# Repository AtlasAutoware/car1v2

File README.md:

# Atlas car 1 v2

Car 1 v2 is the rebuild of car 1, Atlas Autoware's 1/10-scale self-driving race car: a Traxxas Slash 4x4 with a
Holmes Hobbies Puller Pro 540 motor on a carbon-fibre-printed deck, carrying car 1's RPLidar C1 and OAK-D Pro. There
is one car. This repository was named `carv2` until 11 November 2026, and its older files call the car "car v2" or
"car 2". The SICK TiM561 lidar and the LUCID Triton camera that the first design was drawn around are kept for a
later upgrade. Start at `docs/CAR1V2.md`.

Rev B (October 2026) is the electronics design car 1 v2 starts from. Its electronics are:

- **Power board (ATLAS-PWR-1).** A 4-layer board that students solder at school: the motor-bus switch with
  precharge and a hardware E-stop, the power latch, the feeds for the Jetson, lidar, camera, servo and fan, USB-C
  charging, a USB hub so one laptop cable reaches the Jetson, the ESC and the serial console, and a Raspberry Pi Pico
  that sequences it all and talks to the Jetson.
- **The Jetson Orin Nano Super on its NVIDIA dev-kit carrier,** which the team owns, on a printed tray over the power
  board.
- **The team's Flipsky Mini FSESC 6.7 Pro** as the ESC (VESC firmware, the same UART commands as car 1).
- **A JBD 4S smart BMS** with the built-in 4S3P 18650 pack.

`docs/REV_B.md` has the whole design and why it changed. Rev A (two custom boards: a 6-layer drive board with the ESC
on it and an 8-layer Jetson carrier) was finished in September, quoted by PCBWay at $1,927.81 for one assembled set,
and is kept in the repo as history.

The picture is car 1 v2 as designed on 9 November 2026 (`share/car1v2_scene.py`, `share/render_car.py`). Bought
parts are stand-ins, and the battery, the BMS, the fuse and the cables are not drawn. The rev A renders are
`share/car_*.png`.

## Status

**11 November 2026: the repository is renamed from `carv2` to `car1v2`.** GitHub redirects the old address. Whole-car
renders of car 1 v2 are in `share/car1v2_*.png`, and KiCad 3D renders of the power board are in
`boards/power/out/render/power_iso.png` and `power_top.png`.

**9 November 2026: car 1 v2 is designed and priced on the `rev-b-tht` branch; nothing is ordered, built or merged.**

Car 1 v2 is the rebuild of car 1 on this rev B design. It keeps car 1's RPLidar C1 and OAK-D Pro (the SICK lidar
and the LUCID camera named above are kept for later), runs from a 4S LiPo the team owns behind a JK smart BMS, and
uses the second Jetson dev kit. Start at `docs/CAR1V2.md`.

- Money: stage 1 comes to $967.72 against a $1,500 limit, and $1,272.50 if every estimate turns out badly
  (`bom/car1v2/BUDGET.md`, one cart file per supplier). Five bare boards were quoted on 9 November at $182.34
  (PCBWay) and $117.39 (JLCPCB), both before duty.
- Power board: the copper is unchanged. Three values changed after the review (R419 is 470 ohm, C405 is 150 uF, and
  the capacitor part numbers are ones in stock), and KiCad 10 was re-run on the team laptop on 9 November: ERC 0
  errors, DRC 0 errors, 0 unconnected, 0 schematic parity issues, 47 silkscreen warnings. Parts are $149.40 a board.
- An independent review (`docs/review_car1v2_2026-11-09.md`) checked the schematic, the BOM arithmetic and the budget
  and said "pass with fixes" on each. What was done about every finding is at the end of `docs/CAR1V2.md`.
- The supervisor firmware passes 129 tests on a simulated board. It has not run on a Pico.
- Speed (`docs/PERFORMANCE.md`): on 15/54 gearing the model reaches the 12.5 to 13.5 m/s target, 1.5 to 2.5 m/s
  above the 11 m/s competition benchmark. At equal grip it only matches a standard competition car round a lap, and
  the E-stop does not brake, so it is not safe to run at that speed yet. The mass (5.15 kg), the grip and the motor
  resistance in the model are not measured.
- Aero and cooling (`docs/AERO.md`): four CFD cases at 8 m/s. The wing is left off.
- For the builders: `docs/CAR1V2_QUICK_START.md` (short), `docs/CAR1V2_BUILD.md` (session by session),
  `docs/CAR1V2_CHECKLIST.md` (what to confirm, measure and test by hand), `docs/CAR1V2_WIRING.md`, and a named 3D
  assembly in `mech/out/car1v2/assembly/` (the battery, BMS, fuse and cables are not in it).
- Not verified yet: the bank balance on the day, the LiPo's size and type, the pinion and spur on the chassis, the
  duty rates, and the small-parts prices, which are estimates. `docs/CAR1V2.md` ends with the full list.

**26 October 2026: the rev B power board is routed and its order files are made; nothing is ordered or built yet.**

- An independent pre-order review (`docs/review_revb_2026-10-24.md`) said "fix first, then order; no redesign is
  needed". Its one blocker and seven majors are fixed in the design and the firmware (`boards/power/DESIGN_FIXED.md`,
  `firmware/supervisor/NOTES.md`). It asks for three bench tests before ordering; they are listed in `docs/REV_B.md`.
- The power board is designed and routed (`boards/power/`). `netcheck.py` finds 0 errors and 14 warnings (small
  back-power currents into unpowered pins, all within its limits). It is routed on four layers (2 oz outside, a 1 oz
  ground plane and a 1 oz signal layer inside; two attempts on two layers left 18-21 logic nets open round the Pico),
  and KiCad's DRC finds 0 unconnected items and 0 clearance errors (`boards/power/LAYOUT_NOTES.md`). Parts cost
  $149.37 per board at quantity 1 (`bom/revb/power_board_cost.md`); PCBWay's instant quote for five bare boards is
  $182.34 with shipping. The order files are in `boards/power/out/fab/`, renders in `boards/power/out/render/`.
- Before the boards are ordered: ERC and the KiCad 10 DRC with schematic parity on the team laptop
  (`boards/tools/run_kicad.sh erc-power` and `drc-power`; KiCad 7, used for the layout, cannot read the schematic
  sheets).
- The supervisor firmware (`firmware/supervisor/`) passes its 119 tests on a simulated board. It has not run on a
  Pico.
- The Jetson tools (`software/jetson/`) are rewritten for the dev-kit carrier and the supervisor and pass their tests,
  including the real firmware run against them over a pseudo-terminal. Nothing has run on the car.
- The printed kit (`mech/`) is redone for the dev-kit tray, the ESC cradle and the BMS holder. With a 130 mm power
  board both scripts find zero interference. The tray, the BMS holder, the canopy and the splice plates can also be
  laser-cut from 3 mm sheet, and a 3 mm acrylic shield over the live FET bar is always cut (`mech/README.md`,
  "Laser-cut parts"). The dev-kit carrier's hole positions are placeholders until the owned
  board is measured.
- Still to measure before ordering and printing: `docs/MEASURE_FIRST.md`, items 12 and 17-31. The open questions are
  at the end of `docs/REV_B.md`.

## What is in here

| folder | what |
| --- | --- |
| `docs/` | `REV_B.md` (the rev B design and why), `review_revb_2026-10-24.md` (the independent pre-order review), `BUILD_POWER_BOARD.md` (student assembly guide for the power board), `SOFTWARE.md` (what runs on the car), `FLASHING.md` (programming the Pico, the FSESC and the Jetson), `WIRING.md` (every cable run and its length), `MEASURE_FIRST.md` (numbers to check before printing and ordering), `PACK_BUILD.md` (building the 18650 pack); rev A: `ARCHITECTURE.md`, `TPS25751_CONFIG.md`, `COMPLETE_CAR.md` |
| `boards/power/` | rev B power board: `design.py` is the circuit (every value with its reason), `layout.py` the placement and power copper, `PINMAP.md` the Pico pin map, `README.md` the bench tests, `netcheck.py` the electrical checks; the KiCad schematic is generated from them |
| `firmware/supervisor/` | MicroPython for the Pico on the power board: power sequencing, E-stop latch, BMS reading, the USB link to the Jetson; a simulator and tests that run on a PC |
| `software/jetson/` | the `atlas` command, services and settings for the Jetson (`system/install.sh`), with tests |
| `software/ros2/` | `atlas_power`: battery, E-stop, charging and lidar power in ROS 2 |
| `mech/` | the printed kit: `kit.py` (deck, pods, mounts, pack box, dev-kit tray, ESC cradle, BMS holder) and `extras.py` (canopy, bench stand, plugs and cable paths); `NOTES_REVB.md` has the rev B changes and print list |
| `bom/` | rev A parts list and cost summary; `bom/revb/` the power board's parts and cost per block; `bom/car1v2/` the car 1 v2 budget and one cart per supplier; `cost_summary.md` has both revisions |
| `boards/tools/` | the scripts that build, place, route and check the boards |
| `boards/drive/`, `boards/brain/`, `boards/stack/`, `firmware/vesc/` | rev A (history): the drive board with its VESC target, the Jetson carrier forked from Antmicro's design, and the connector between them |
| `sim/` | rev A circuit and thermal checks; `sim/aero/` the car 1 v2 CFD cases and `sim/perf/` its speed and lap model |
| `share/` | pictures for posting; `car_scene.py` and `render_car.py` render the whole car (rev A; not yet updated) |

## Cost

From `bom/cost_summary.md` and `docs/REV_B.md` (prices from September and October 2026):

| | rev A | rev B |
| --- | ---: | ---: |
| Electronics for one car (rev A: one assembled PCBWay set; rev B: power board parts, BMS, BEC, fuse, leads, lidar adapter, camera cable, and the order of five bare boards) | 1,927.81 | 523.27 |
| Pack materials, lens, charger, fan, hardware, antennas | 402.55 | 376.56 |
| Castle Link (one-time, to set the servo BEC) | | 26.99 |
| **One car, new money** | **2,330.36** | **926.82** |
| **Two cars, new money** (one bare-board order for both) | **about 3,205** | **1,644.31** |

The ESC and the Jetson dev kit are owned and cost nothing new. Assembly is done by students at school. The five bare
boards are PCBWay's instant quote of October 26 ($155.79 + $26.55 DHL), before the Future Innovators discount and
customs.

## Rebuilding

Rev B:

- **Power board design files.** KiCad 7 or later and Python 3, from `boards/tools`:
  ```
  python3 make_footprints.py power
  KICAD_STOCK_SYMBOLS=/usr/share/kicad/symbols python3 build_sch.py power
  KICAD_FP_DIR=/usr/share/kicad/footprints python3 check_fp.py power
  KICAD_FP_DIR=/usr/share/kicad/footprints python3 fp_lib_from_mod.py power    # first run only
  python3 placer.py power --plot ../power/out/placement.png
  python3 ../power/netcheck.py
  python3 ../../bom/revb/make_power_bom.py
  ```
    The board is routed: do not run `placer.py` or `build_pcb.py` again unless the layout is to be redone, because they
  rebuild the board from the placement and drop the routing (`boards/power/LAYOUT_NOTES.md`, "Regenerating"). The
  order files come from `python3 fab_outputs.py power` (KiCad 7 or later). On the laptop with KiCad 10, from the repo
  root: `boards/tools/run_kicad.sh erc-power` and `boards/tools/run_kicad.sh drc-power` before ordering; not
  `pcb-power` or `fab-power`.
- **Printed kit.** `pip install cadquery ezdxf shapely matplotlib`, then from `mech/`:
  `python3 kit.py`, `python3 extras.py` and `python3 ../boards/board_outlines.py` (the default board length is the
  layout's 130 mm; `SHEET_PARTS=all` checks the laser-cut parts in place of the printed ones).
- **Supervisor firmware.** `python3 -m pytest firmware/supervisor/tests`. To put it on a Pico: MicroPython from
  micropython.org, then `mpremote connect /dev/ttyACM0 cp pins.py hal.py jbd.py link.py sequencer.py main.py :` from
  `firmware/supervisor/` (`firmware/supervisor/README.md`).
- **Jetson tools.** `sudo software/jetson/system/install.sh` on the car; tests with
  `python3 -m pytest software/jetson/tests` (needs `pytest`).

Rev A (history):

- Boards: KiCad 10 and Python 3. `boards/tools/run_kicad.sh` runs every step (schematic, board, routing export and
  import, DRC, renders, fabrication files). Careful with `pcb-drive`: it builds the board again from the placement,
  without the routing.
- VESC target: `firmware/vesc/build.sh` (clones VESC 6.06, adds the two target files, builds; needs
  `arm-none-eabi-gcc`). A build of the committed sources is in `firmware/vesc/prebuilt/`.
- Simulations: ngspice and Python with numpy, scipy and matplotlib; `sim/run_all.sh`.
- Whole-car renders: `python3 share/car_scene.py`, then `python3 share/render_car.py -- car_front_left car_exploded`
  with Blender 4.2's `bpy` module. These use the rev A model and no longer run against the rev B kit.

## Licenses

The brain board is derived from Antmicro's Jetson Orin Baseboard (Apache-2.0); its schematic and
board keep Antmicro's notices, and `boards/brain/vendor/antmicro/fetch.sh` downloads the original. The VESC
hardware target is derived from the VESC firmware (GPL-3.0), so those two files are GPL-3.0.

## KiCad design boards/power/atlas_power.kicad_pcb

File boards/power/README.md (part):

# ATLAS-PWR-1 power board (rev B)

The rev B power board sits on the deck under the Jetson dev kit's printed tray. It takes the 4S pack (through the
pack's XT90-S, 125 A fuse and JBD BMS), switches the motor bus for the Flipsky FSESC with a hardware E-stop,
latches the car on and off from a push button, feeds the dev kit, lidar, camera, servo BEC and fan, charges the
pack from USB-C, gives the laptop one USB-C cable to the dev kit, the VESC and a serial console, and carries the
Raspberry Pi Pico supervisor that sequences all of it and talks to the Jetson.

Source of truth: `design.py` (netlist, parts, values and their reasons), `layout.py` (placement, power copper,
outline), `PINMAP.md` (Pico GPIO map). `NOTES.md` has the judgment calls and open questions, `HANDOFF_E.md` what
the layout and routing step needs.

## At a glance

| | |
| --- | --- |
| Size | 130 x 84 mm, 4 layers, 1.6 mm, HASL lead-free. Six M3 holes at (4,4), (4,80), (75,4), (75,80), (126,4), (126,80) with 7 mm keep-outs |
| Layers | 4: F.Cu and B.Cu 2 oz (parts, the BAT/VM/GND power pours), In1.Cu 1 oz solid GND plane (cut out under the BMS domain), In2.Cu 1 oz signals. Four because on two layers the logic half round the Pico could not be routed (21 connections still open after two full attempts) and its ground had no path to the pack (LAYOUT_NOTES.md) |
| Parts | 80 through-hole parts on the top (3 of them DIP sockets); 104 chip resistors and capacitors (1206, five 1210) on the bottom; Pico and USB hub modules on 8.5 mm sockets; 4 modules wired off the board (Pololu latch, camera 12 V regulator, PD trigger, CC/CV buck); a 40 x 15 x 3 mm aluminium bar; plus 11 wire pads, 7 bare test pads and 6 holes |
| Tallest parts | the three 680 uF capacitors (12.5 x 20 mm, about 21 mm installed) and the FETs on their bar (about 20 mm). Everything is under the 23 mm limit of the dev-kit tray |
| Parts cost | USD 149.37 per board at quantity 1 (USD 11.30 of it not verified), table below; the bare PCB is quoted by the layout step |
| Checks | `netcheck.py`: 0 errors, 14 warnings: back-power of 0.05-0.28 mA (below the 0.5 mA limit), and 2.7 mA into the dev kit's 1k-fed inputs while the dev kit is off (allowed: TXB-type inputs, see NOTES) |

Through-hole first, with one exception: the 130 mm length limit leaves no room for about 100 resistors and small
capacitors as through-hole parts, so they are 1206 chips (1210 for the 10 uF) on the bottom side, with the
longer hand-solder pads. They solder with an iron and tweezers. Every IC is a DIP or TO-92/TO-220 part (the
MIC5014, 74HCT08 and MCP2221A in DIP sockets, which are BOM lines), and the two modules with fine-pitch chips (Pico,
hub) are socketed. The pre-order review (`docs/review_revb_2026-10-24.md`) and what changed for it: `DESIGN_FIXED.md`.

## Blocks

| Block | What it does |
| --- | --- |
| A pack input | 10 AWG pads for a pigtail with an XT90 male, which plugs into the XT90-S female on the pack (the female holds the anti-spark resistor); 3 x 680 uF 35 V low-ESR + 1 uF at the pads; 1.5KE20A TVS |
| B BMS link | JBD UART on a JST-XH 4 through two PC817s: the BMS side switches B-, so its ground never meets board ground |
| C main switch | 3 x IRFB7430 (TO-220, on one bar) high-side, driven by a MIC5014 (DIP-8); precharge IRF9Z34N + MF-R050 + 10 Ohm 5 W; a 74HCT08 ANDs the Pico enables with the E-stop loop in hardware; 1.5KE22A on the motor bus; NTC on the bar |
| D latch and rails | Pololu #2813 push-on latch (off board) gives VSYS_SW; RECOM R-78E 5 V behind 4.7 Ohm + P6KE20A; Castle BEC pads (BEC+ on VM, or the alternative BEC+ALT pad on VSYS_SW) and the servo header with 1000 uF; dev-kit feed: 5 A mini blade fuse, P6KE22A, over-voltage cut-off (IRF4905, TL431, trips 18.7 V, releases 17.85 V, 100 nF soft start) that is also the Pico's power-cycle switch; lidar high-side switch with polyfuse and P6KE22A; camera 12 V regulator (Pololu S18V20F12, off board) behind a polyfuse and a P6KE22A |
| E charging | USB-C PD trigger (Adafruit 5807, 20 V) and an XL4015-class CC/CV buck set to 16.80 V / 2.5 A, both off the board in the side pod. The charger side has its own ground, CHG_GND, joined to GND only through the buck's IN- to OUT- (its current shunt), so constant current works. Reverse block IRF4905 that turns fully on only with 20 V present; 5 A fuse into the pack bus; CHG_PRESENT_N to the Pico |
| F debug | Adafruit 5997 CH334F hub (bus powered by the laptop, its USB-C is the laptop port): port 1 on a through-hole USB-A receptacle (one standard USB-A to USB-C cable to the dev kit), port 3 on a 1x4 header to the FSESC (its ground through 2.2 Ohm), port 2 to an MCP2221A console on the dev kit's J14 UART, port 4 spare |
| G supervisor | Raspberry Pi Pico in sockets, ADC dividers for VM and the pack, status and fault LEDs |
| H Jetson | 2x20 shrouded box header for the J12 ribbon (7 pins left open so a reversed ribbon shorts nothing), 1k on the board outputs toward the Jetson (the dev kit level-shifts them), 10k on its outputs toward the board; 1x12 header for the J14 harness with PC817s for the power key and reset, recovery button |
| I ESC | 10 AWG pads for the FSESC, its COMM lead (UART pass-through to J12 pins 8/10, ADC2 kill line), servo-signal input. The COMM and servo-lead grounds go to GND through 3.3 Ohm each, so motor current stays in the ESC- lead |
| J misc | E-stop loop (JST-PH 2), remote button (JST-PH 2, side entry), 4-pin fan header with PWM, holes, test loops |

## Build the design files

From `boards/tools` (KiCad 7 or later installed; the schematic files are KiCad 9 format):

```
python3 make_footprints.py power                                            # this board's footprints in lib/atlas.pretty
KICAD_STOCK_SYMBOLS=/usr/share/kicad/symbols python3 build_sch.py power      # schematic sheets + atlas_power_parts.json
KICAD_FP_DIR=/usr/share/kicad/footprints python3 check_fp.py power           # every footprint exists and matches its symbol
KICAD_FP_DIR=/usr/share/kicad/footprints python3 fp_lib_from_mod.py power    # footprint geometry for the placer (first run only)
python3 placer.py power --plot ../power/out/placement.png                    # placement and power copper (out/*.json)
python3 ../power/netcheck.py                                                 # electrical checks (exits 1 on an error)
python3 ../../bom/revb/make_power_bom.py                                     # bom/revb: BOM CSV and cost per block
```

The PCB itself (build_pcb.py inside KiCad, routing, DRC, fab files) is the layout step: `LAYOUT_NOTES.md` has how
the board was built and routed, the DRC result, the high-current numbers and what to run again on the laptop
(KiCad 10); `HANDOFF_E.md` has the placement brief it started from.

## Assembly order (short; the student guide is docs/BUILD_POWER_BOARD.md)

1. Bottom side first: the 1206/1210 chips (flux, tweezers, iron at about 330 C). Check each against the bottom
   silkscreen; nothing is polarised.
2. The parts that sit under the modules, before their sockets: U302 socket and U801/U802 under the Pico; U601
   socket and U602 under the hub. Keep everything under a module 9 mm tall or less.
3. Low through-hole parts, then sockets and headers, then the TO-92s, TVS diodes, LEDs, fuse holders, R313 and the
   electrolytics (watch the polarity), then the three main FETs bolted to the bar before their legs are soldered.
4. Wire pads last: pack pigtail (10 AWG), ESC (10-12 AWG), BEC and servo leads (16 AWG), dev-kit lead (18 AWG),
   then the off-board modules. The four 10 AWG pads (J101, J102, J901, J902) sit solid in 2 oz pours: preheat the
   board to about 100 C on a hot plate or use a 100-150 W iron; a 70 W iron may not wet them (review m19).

## Settings that must be made before the first drive

| Where | Setting | Why |
| --- | --- | --- |
| JBD BMS (app) | cell over-voltage 4.25 V | above the 4.20 V the charger ends at, so a cell running slightly high does not end the charge or remove regen on a full pack (review m12) |
| CC/CV buck (trimmers, on the bench) | 16.80 V constant voltage, 2.5 A constant current | 4.20 V per cell; set CV with no load, CC into a load bank or a 4.7 Ohm resistor rated 50 W (about 30 W at 2.5 A, so only briefly) |
| FSESC (VESC Tool) | maximum input voltage 18 V | the VESC limits regenerative braking to keep the bus under this, so regen on a full pack stays below the pack TVS (19-21 V) and the dev-kit cut-off (18.7 V) (review m4) |
| FSESC (VESC Tool) | battery cut-off start 13.4 V, end 12.6 V | keeps a sagging pack from pulling VSYS_SW under the dev kit's 9 V and the R-78E's 8 V (review m9) |

## Before wiring the charger: check the CC/CV module (review B1)

The board expects a CC/CV module that senses its output current with a shunt between IN- and OUT- (the common
XL4015 board with two trimmers and an LM358) and gives the charger side its own ground for it. Check the module in
hand: 20 V into IN+/IN-, a 4.7 Ohm power resistor (50 W, briefly) on OUT+/OUT-, then measure from IN- to OUT-. About
0.1 V means a low-side shunt (this board's case: fine). About 0 V with the current still limited by the CC trimmer
means high-side sensing (also fine: IN- and OUT- are joined inside, the CHG_GND pads still work). If the current does
not follow the CC trimmer at all, do not use that module. No alternative module whose published schematic shows
high-side sensing could be verified, so none is named (see NOTES).

## Three bench tests before the pack goes on

Use a bench supply with a current limit for tests 1 and 2. Keep the FSESC, the dev kit and the pack disconnected
until test 2 has passed.

### 1. Logic only, from a 5 V bench supply

Do this before U401 (R-78E) is fitted, so the bench supply does not feed the regulator's output.

1. 5.0 V, limit 0.3 A, into TP402 (+5V) and TP1002 (GND). The green 5 V LED lights; supply current under about
   120 mA with the fan unplugged. TP701 (+3V3) reads 3.2-3.4 V once the Pico runs.
2. E-stop: with a jumper lead in J1001, GP10 (ESTOP_OK) reads about 3.0 V; without it, 0 V.
3. From the Pico REPL drive GP3 (MAIN_EN) high: U301 pin 2 (MIC5014 IN) reads about 4.9 V with the loop closed and
   0 V with it open. Same for GP2: Q305's base gets about 0.7 V only with the loop closed. Set both low again.
4. GP17 and GP18 light the status and fault LEDs; GP14 sets FSESC COMM pin 6 to 3.3 V; GP16 drives the fan.
5. BMS link loop-back: power J201's BMS side from a separate 3.3-5 V source (a USB power bank: J201 pin 1 = +,
   pin 4 = -, never joined to board GND) and bridge J201 pins 2 and 3. Bytes sent on UART0 at 9600 baud come back.
6. Laptop on the hub's USB-C: the hub and a USB serial port (MCP2221A) appear. With the bench supply off and only
   the laptop plugged in, TP402 stays at 0 V (the laptop never powers the car).
7. Later, with the dev kit: one USB-A to USB-C cable from J601 to the dev kit's USB-C gives 192.168.55.1. For
   flashing, NVIDIA documents a direct cable; if flashing through the hub fails, plug the laptop straight into the
   dev kit (review M7).

### 2. Pack bus from a current-limited 14 V at 0.5 A: latch, precharge, main switch

Fit U401 and wire the Pololu #2813 (VIN, VOUT, GND, ON, OFF). Bench supply 14.0 V, limit 0.5 A, on J101/J102.
Dummy load on the ESC pads: 1000 uF 35 V in parallel with 100 Ohm 2 W. Drive the Pico's pins from its REPL
(MicroPython only, before the supervisor files are copied), as in `docs/BUILD_POWER_BOARD.md`.

1. Off state: record the supply current (Pololu off current plus leakage). Nothing on VSYS_SW (TP401). If the latch
   switches itself on when the supply is applied, write that down (review m17).
2. Press SW401: TP401 = 14 V, TP402 = 5 V, the Pico boots.
3. Precharge (loop in J1001, GP2 high): VM (TP301) rises with a time constant of about 10 ms and settles near 12.7 V
   (10.5 Ohm against the 100 Ohm load). Then GP3 high: TP302 (SW_GATE) reads 13-17 V above VM and VM = 14 V; GP2
   low.
4. Open the E-stop loop: VM falls to 0 V. **Set GP3 low before the loop closes again**: at the REPL nothing drops
   GP3, and with GP3 still high the 74HCT08 recloses the switch the moment the loop closes. (The supervisor firmware
   drops MAIN_EN as soon as the loop opens and waits for a button press.)
5. At 12.0 V, repeat step 3: SW_GATE must still be at least 10 V above VM (review m1). Back to 14.0 V, GP3 low.
6. Dev-kit feed, with a load of about 1 kOhm 0.5 W or more across DEV+ and DEV- (without one, C405 holds DEV+ up
   after the feed is cut): DEV+ = 14 V; GP22 low cuts it to 0 V. With GP3 low, raise the supply slowly: DEV+ drops to
   0 V at about 18.7 V and returns at about 17.85 V on the way down. Stop at 19.0 V (the pack TVS starts to conduct
   above 19 V).
7. GP6 high puts 14 V on the lidar terminal; the camera pads carry 14 V through F403.
8. GP9 pulse: the latch turns everything off.
9. Precharge into the real loads (review M3; test 4 in `docs/BUILD_POWER_BOARD.md`): at 12.0 V, with the supply's
   limit above the precharge peak (about 1.1 A), replace the dummy load with the FSESC, the Castle BEC (set to 7.5 V)
   with the servo and the 1000 uF, scope on VM. Precharge must bring VM to within 2.5 V of the supply and stop rising.
   If the BEC's start-up holds VM down, move the BEC's red lead from BEC+ (J401, on VM) to BEC+ALT (J410, on
   VSYS_SW; the latch, rated 6 A continuous, then carries the servo as well as the dev kit, lidar and camera, so
   check that sum at a 12 V pack), or fit a 4.7 Ohm 5 W cement resistor (Yageo SQP500JB-4R7, same body) as R313
   (3.6 A peak for about 10 ms; check that F301, the MF-R050, does not trip). Then, with only the laptop on the
   FSESC's USB (everything else off), measure VM: above 1 V means the FSESC feeds its USB power back into the motor
   bus; cut the VBUS wire in the FSESC's USB lead (review m14).

### 3. Main switch under load: 50 A, then 70 A pulses, thermocouple on the FETs

Use the real pack (its BMS, 125 A fuse and XT90-S in place) or a supply that can deliver 70 A, a load bank on the
ESC pads (about 0.33 Ohm for 50 A, 0.24 Ohm for 70 A, rated for the pulse energy), and a thermocouple taped with
Kapton to the middle FET's tab (the bar is BAT+; a second one on C101 if you have it). Two people, eye protection,
an adult supervising, and a way to open the E-stop loop from a distance.

The pulses come from the load's own switch (a switch or contactor rated for 70 A DC, or an electronic load's pulse
mode), never from the main switch. With the load's switch open, switch the car on, precharge and close the main
switch (GP2, then GP3, then GP2 low; or the supervisor firmware); it then stays closed for the whole test, as in the
car, where it closes after precharge with the ESC idle and only opens under load when the E-stop is pulled. Closing
the main switch straight into a 50 A load is not part of the test.

1. 50 A for 2 s, 20 s off, ten times. Watch SW_GATE minus VM (at least 10 V), the drop from BAT to VM (expect
   tens of mV), and the tab temperature (it should not climb more than about 20 C over the run). Compare the
   FET_NTC reading with the thermocouple.
2. 70 A for 1 s, 30 s off, five times, same checks.
3. Open the E-stop during a 50 A pulse with a scope on TP101 (BAT) and TP301 (VM): the spike must stay well under
   the TVS clamps (27.7 V at full TVS current); expect a few volts. The FETs' turn-off time (0.1-0.4 ms in
   `design.py`, not verified) shows up here.
4. Pass: no FET tab above 80 C, no hot spot on the VM pour (a thermal camera helps, review m20), switch-off clean.
   Note the capacitor temperature too (review m21).

## Cost per block

Quantity-1 prices read on 2026-10-24 (links in the parts table). Buying for three boards brings the chip resistors
and capacitors down to a few cents each. Not included: the bare PCB, the cables and leads (ribbon, J14 harness,
USB leads, pack pigtail), the BMS, the Castle BEC and the pack hardware, which are car-level items.

| Block | Parts cost (USD) | Of which not verified (USD) |
| --- | ---: | ---: |
| A pack input | 4.76 | 0.00 |
| B BMS link | 1.49 | 0.00 |
| C main switch, precharge, E-stop gate | 24.92 | 2.50 |
| D latch and rails (5 V, servo, dev kit, lidar, camera) | 61.23 | 0.00 |
| E USB-C charging | 21.11 | 8.00 |
| F debug hub and console | 18.76 | 0.30 |
| G Pico supervisor | 8.97 | 0.50 |
| H Jetson ribbon and J14 | 4.04 | 0.00 |
| I ESC interface | 1.06 | 0.00 |
| J E-stop, fan, holes | 3.03 | 0.00 |
| **Total per board** | **149.37** | **11.30** |

## Parts

Generated from `atlas_power_parts.json` by `bom/revb/make_power_bom.py` (the CSV there has descriptions and
reasons). "Verified" = yes: price and part read on the linked page on 2026-10-24; est.: catalogue estimate;
no: not confirmed (the CC/CV module is a generic part, the bar is cut to order).

| Refs | Part | Package | Qty | Unit (USD) | Source | Verified |
| --- | --- | --- | ---: | ---: | --- | --- |
| C101 C102 C103 | 680u 35V, EEU-FM1V681 | CP Radial D12.5mm P5.00mm | 3 | 1.47 | [digikey.com](https://www.digikey.com/en/products/detail/panasonic-industry/EEU-FM1V681/613778) | yes |
| C404 | 1000u 16V, EEU-FM1C102 | CP Radial D10.0mm P5.00mm | 1 | 1.14 | [digikey.com](https://www.digikey.com/en/products/detail/panasonic-industry/EEU-FM1C102/613727) | yes |
| C405 | 150u 35V, Panasonic EEU-FM1V151 | CP Radial D8.0mm P3.50mm | 1 | 0.58 | [digikey.com](https://www.digikey.com/en/products/detail/panasonic-industry/EEU-FM1V151/613769) | yes |
| D1001 D1002 | BAT85S-TAP | D DO-35 SOD27 P2.54mm Vertical KathodeUp | 2 | 0.43 | [findchips.com](https://www.findchips.com/search/BAT85) | yes |
| D101 | 1.5KE20A | D DO-201AD P5.08mm Vertical KathodeUp | 1 | 0.42 | [findchips.com](https://www.findchips.com/search/1.5KE20A) | yes |
| D301 | 1.5KE22A | D DO-201AD P5.08mm Vertical KathodeUp | 1 | 0.29 | [findchips.com](https://www.findchips.com/search/1.5KE22A) | yes |
| D302 D702 | Lite-On LTL-4221N (3 mm red) | LED D3.0mm | 2 | 0.12 | [findchips.com](https://www.findchips.com/search/LTL-4221N) | yes |
| D401 | P6KE20A | D DO-15 P3.81mm Vertical KathodeUp | 1 | 0.54 | [findchips.com](https://www.findchips.com/search/P6KE20A) | yes |
| D402 | 1N5817RLG | D DO-41 SOD81 P3.81mm Vertical KathodeUp | 1 | 0.67 | [findchips.com](https://www.findchips.com/search/1N5817RLG) | yes |
| D403 D701 | Lite-On LTL-4231N (3 mm green) | LED D3.0mm | 2 | 0.10 | [findchips.com](https://www.findchips.com/search/LTL-4231N) | yes |
| D404 D405 D406 | P6KE22A | D DO-15 P3.81mm Vertical KathodeUp | 3 | 0.45 | [findchips.com](https://www.findchips.com/search/P6KE22A) | yes |
| D501 | P6KE24A | D DO-15 P3.81mm Vertical KathodeUp | 1 | 0.54 | [findchips.com](https://www.findchips.com/search/P6KE24A) | yes |
| D502 | 1N5247BTR | D DO-35 SOD27 P2.54mm Vertical KathodeUp | 1 | 0.17 | [findchips.com](https://www.findchips.com/search/1N5247BTR) | yes |
| F301 | MF-R050 | Fuse Bourns MF-R P5.08mm | 1 | 0.47 | [findchips.com](https://www.findchips.com/search/MF-R050) | yes |
| F401 F501 | 5A mini, Keystone 3568 + Littelfuse 0297005.WXNV | Fuseholder Blade Mini Keystone 3568 | 2 | 1.48 | [findchips.com](https://www.findchips.com/search/3568) | yes |
| F402 F403 | MF-R075 | Fuse Bourns MF-R P5.08mm | 2 | 0.25 | [findchips.com](https://www.findchips.com/search/MF-R075) | yes |
| J1001 | B2B-PH-K-S(LF)(SN) | JST PH B2B-PH-K 1x02 P2.00mm Vertical | 1 | 0.12 | [findchips.com](https://www.findchips.com/search/B2B-PH-K-S) | yes |
| J1002 | S2B-PH-K-S(LF)(SN) | JST PH S2B-PH-K 1x02 P2.00mm Horizontal | 1 | 0.12 | [findchips.com](https://www.findchips.com/search/S2B-PH-K-S) | yes |
| J1003 | Molex 47053-1000 | FanPinHeader 1x04 P2.54mm Vertical | 1 | 0.56 | [findchips.com](https://www.findchips.com/search/0470531000) | yes |
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
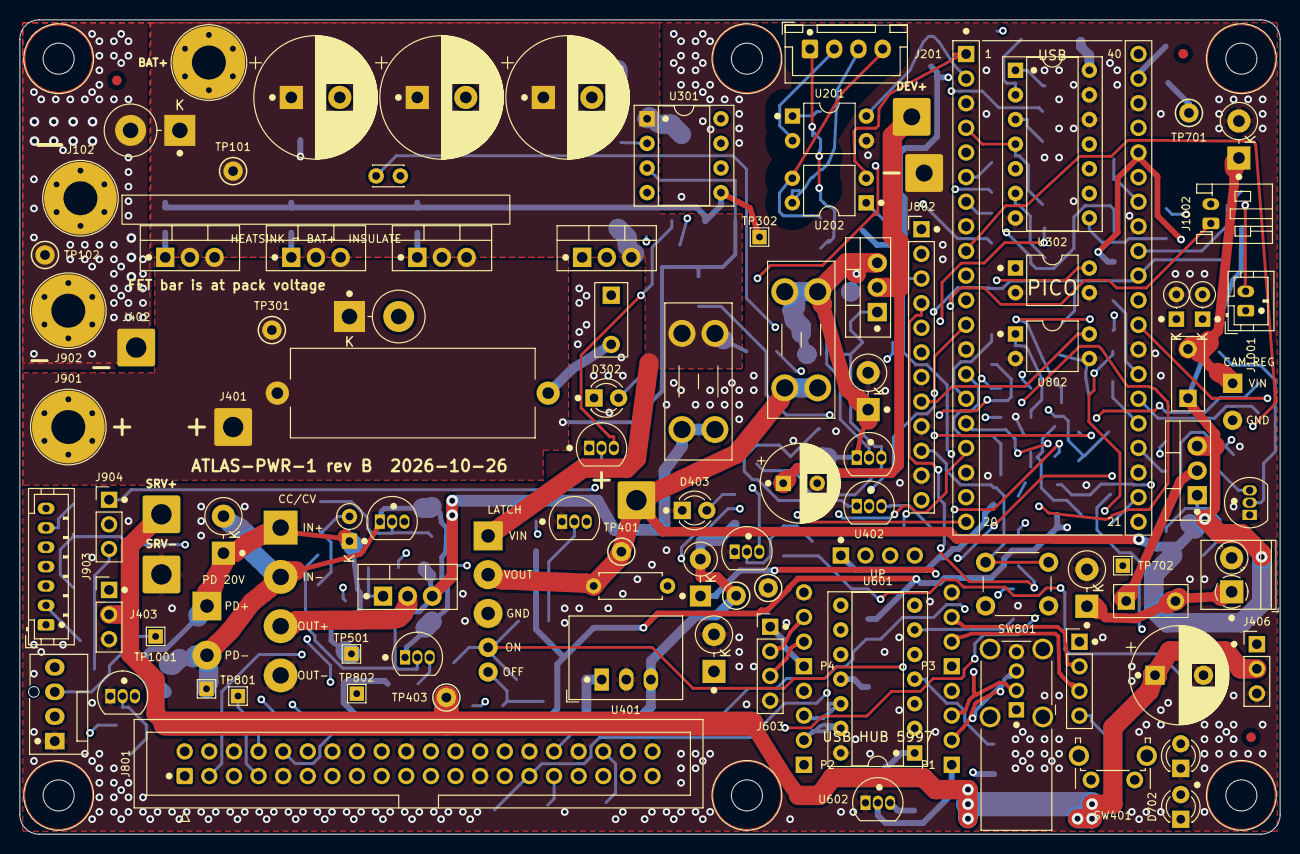
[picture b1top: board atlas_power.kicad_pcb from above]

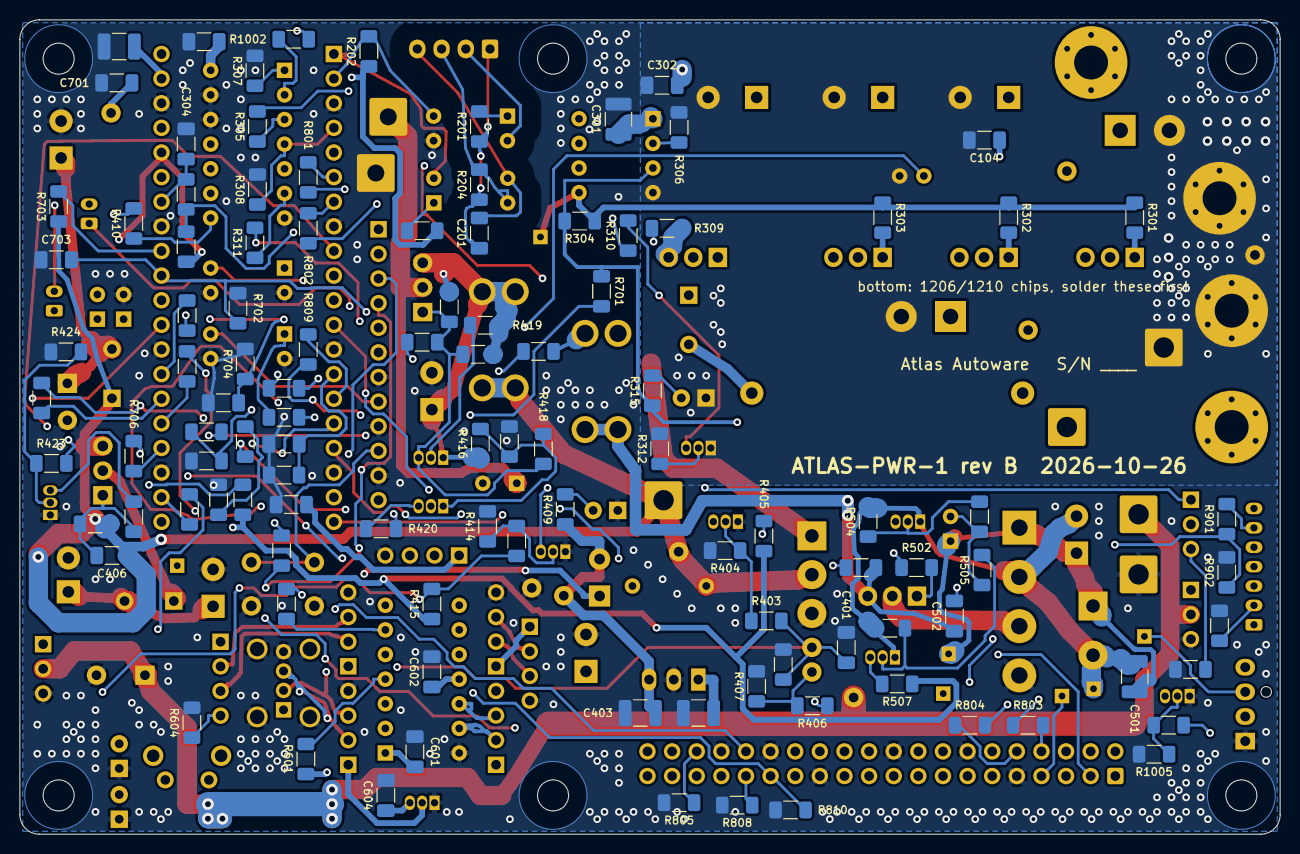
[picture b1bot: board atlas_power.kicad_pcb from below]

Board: 4 copper layers, 130.0 x 84.0 mm, 218 parts (107 on the bottom side), 133 nets.

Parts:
C101, C102, C103: 680u 35V; CP_Radial_D12.5mm_P5.00mm
C104: 1u 50V; C_1206_3216Metric_Pad1.33x1.80mm_HandSolder
C201, C302, C303, C304, C401, C406, C407, C502, C601, C602, C701, C703, C704: 100n; C_1206_3216Metric_Pad1.33x1.80mm_HandSolder
C301, C402, C403, C501, C702: 10u 50V; C_1210_3225Metric_Pad1.33x2.70mm_HandSolder
C404: 1000u 16V; CP_Radial_D10.0mm_P5.00mm
C405: 150u 35V; CP_Radial_D8.0mm_P3.50mm
C603, C604: 1u; C_1206_3216Metric_Pad1.33x1.80mm_HandSolder
C1001: 10n; C_1206_3216Metric_Pad1.33x1.80mm_HandSolder
D101: 1.5KE20A; D_DO-201AD_P5.08mm_Vertical_KathodeUp
D301: 1.5KE22A; D_DO-201AD_P5.08mm_Vertical_KathodeUp
D302, D702: RED; LED_D3.0mm
D401: P6KE20A; D_DO-15_P3.81mm_Vertical_KathodeUp
D402: 1N5817; D_DO-41_SOD81_P3.81mm_Vertical_KathodeUp
D403, D701: GREEN; LED_D3.0mm
D404, D405, D406: P6KE22A; D_DO-15_P3.81mm_Vertical_KathodeUp
D501: P6KE24A; D_DO-15_P3.81mm_Vertical_KathodeUp
D502: 1N5247B; D_DO-35_SOD27_P2.54mm_Vertical_KathodeUp
D1001, D1002: BAT85; D_DO-35_SOD27_P2.54mm_Vertical_KathodeUp
F301: MF-R050; Fuse_Bourns_MF-R_P5.08mm
F401, F501: 5A mini; Fuseholder_Blade_Mini_Keystone_3568
F402, F403: MF-R075; Fuse_Bourns_MF-R_P5.08mm
FID1, FID2, FID3: Fiducial; Fiducial_1mm_Mask2mm
H1001, H1002, H1003, H1004, H1005, H1006: M3; MountingHole_3.2mm_M3_Keepout7mm
HS301: HEATSINK_BAR; Heatsink_Bar_3xTO220_40x15x3mm
J101: BAT+; WirePad_THT_10AWG_D3.5mm_OD7.5mm
J102: BAT-; WirePad_THT_10AWG_D3.5mm_OD7.5mm
J201: BMS_UART; JST_XH_B4B-XH-A_1x04_P2.50mm_Vertical
J401: BEC+; SolderWire-1.5sqmm_1x01_D1.7mm_OD3.9mm
J402: BEC-; SolderWire-1.5sqmm_1x01_D1.7mm_OD3.9mm
J403: BEC_OUT; PinHeader_1x03_P2.54mm_Vertical
J404: SRV+; SolderWire-1.5sqmm_1x01_D1.7mm_OD3.9mm
J405: SRV-; SolderWire-1.5sqmm_1x01_D1.7mm_OD3.9mm
J406: SERVO; PinHeader_1x03_P2.54mm_Vertical
J407: DEV+; SolderWire-1sqmm_1x01_D1.4mm_OD3.9mm
J408: DEV-; SolderWire-1sqmm_1x01_D1.4mm_OD3.9mm
J409: LIDAR_PWR; TerminalBlock_Phoenix_PT-1,5-2-3.5-H_1x02_P3.50mm_Horizontal
J410: BEC+ALT; SolderWire-1.5sqmm_1x01_D1.7mm_OD3.9mm
J601: DEVKIT_USB; USB_A_Wuerth_614004134726_Horizontal
J602: VESC_USB; PinHeader_1x04_P2.54mm_Vertical
J603: HUB_PORT4; PinHeader_1x04_P2.54mm_Vertical
J801: J12_RIBBON; IDC-Header_2x20_P2.54mm_Vertical
J802: J14_HARNESS; PinHeader_1x12_P2.54mm_Vertical
J901: ESC+; WirePad_THT_10AWG_D3.5mm_OD7.5mm
J902: ESC-; WirePad_THT_10AWG_D3.5mm_OD7.5mm
J903: FSESC_COMM; JST_PH_B7B-PH-K_1x07_P2.00mm_Vertical
J904: SERVO_IN; PinHeader_1x03_P2.54mm_Vertical
J1001: ESTOP; JST_PH_B2B-PH-K_1x02_P2.00mm_Vertical
J1002: BTN_REMOTE; JST_PH_S2B-PH-K_1x02_P2.00mm_Horizontal
J1003: FAN; FanPinHeader_1x04_P2.54mm_Vertical
MOD401: POLOLU_2813; WireLand_Pololu_2813
MOD402: POLOLU_S18V20F12; WireLand_Pololu_S18V20F12
MOD501: ADA5807_HUSB238; WireLand_PD_Trigger
MOD502: CCCV_BUCK_XL4015; WireLand_CCCV_Buck
MOD601: ADA5997_CH334F_HUB; Adafruit_5997_CH334F_Hub_Headers
MOD701: RPi_Pico; RaspberryPi_Pico_Socketed_2x20_P17.78mm
Q301, Q302, Q303: IRFB7430PBF; TO-220-3_Vertical
Q304, Q405: IRF9Z34NPBF; TO-220-3_Vertical
Q305, Q401, Q403, Q406, Q502, Q503: 2N3904; TO-92_Inline
Q402, Q501: IRF4905PBF; TO-220-3_Vertical
Q404: 2N3906; TO-92_Inline
Q1001: 2N7000; TO-92_Inline
R201, R305, R406, R602, R804, R805, R812, R813, R901, R1001: 1k; R_1206_3216Metric_Pad1.30x1.75mm_HandSolder
R202, R204, R311, R315, R413, R420, R423: 4.7k; R_1206_3216Metric_Pad1.30x1.75mm_HandSolder
R203, R419, R705, R706, R814, R815: 470; R_1206_3216Metric_Pad1.30x1.75mm_HandSolder
R301, R302, R303: 10; R_1206_3216Metric_Pad1.30x1.75mm_HandSolder
R304: 2.2M; R_1206_3216Metric_Pad1.30x1.75mm_HandSolder
R306, R307, R308, R312, R404, R407, R414, R416, R424, R701, R703, R807, R808, R810, R902, R904, R1005: 100k; R_1206_3216Metric_Pad1.30x1.75mm_HandSolder
R309, R310, R314, R316, R402, R405, R411, R415, R421, R422, R501, R507, R601, R603, R803, R806, R809, R811, R903, R1003: 10k; R_1206_3216Metric_Pad1.30x1.75mm_HandSolder
R313: 10 5W; R_Axial_Power_L25.0mm_W9.0mm_P27.94mm
R401: 33k; R_1206_3216Metric_Pad1.30x1.75mm_HandSolder
R403: 22k; R_1206_3216Metric_Pad1.30x1.75mm_HandSolder
R408: 4.7; R_Axial_DIN0207_L6.3mm_D2.5mm_P7.62mm_Horizontal
R409: 2.2k; R_1206_3216Metric_Pad1.30x1.75mm_HandSolder
R410: 220; R_1206_3216Metric_Pad1.30x1.75mm_HandSolder
R412, R502: 6.8k; R_1206_3216Metric_Pad1.30x1.75mm_HandSolder
R417: 15.0k; R_1206_3216Metric_Pad1.30x1.75mm_HandSolder
R418: 1.2M; R_1206_3216Metric_Pad1.30x1.75mm_HandSolder
R503, R504, R505, R506: 47k; R_1206_3216Metric_Pad1.30x1.75mm_HandSolder
R604: 2.2; R_1206_3216Metric_Pad1.30x1.75mm_HandSolder
R702, R704: 18k; R_1206_3216Metric_Pad1.30x1.75mm_HandSolder
R801, R802: 330; R_1206_3216Metric_Pad1.30x1.75mm_HandSolder
R905, R906: 3.3; R_1206_3216Metric_Pad1.30x1.75mm_HandSolder
R1002, R1004: 100; R_1206_3216Metric_Pad1.30x1.75mm_HandSolder
SW401: POWER; SW_Tactile_SPST_Angled_PTS645Vx58-2LFS
SW801: RECOVERY; SW_PUSH_6mm_H5mm
TH301: 10k B3977; C_Disc_D3.0mm_W2.0mm_P2.50mm
TP101: BAT; TestPoint_Keystone_5000-5004_Miniature
TP102, TP1002: GND; TestPoint_Keystone_5000-5004_Miniature
TP301: VM; TestPoint_Keystone_5000-5004_Miniature
TP302: SW_GATE; TestPoint_THTPad_1.5x1.5mm_Drill0.7mm
TP401: VSYS_SW; TestPoint_Keystone_5000-5004_Miniature
TP402: +5V; TestPoint_Keystone_5000-5004_Miniature
TP403: SERVO_V; TestPoint_Keystone_5000-5004_Miniature
TP501: CHG_IN; TestPoint_THTPad_1.5x1.5mm_Drill0.7mm
TP502: CHG_GND; TestPoint_THTPad_1.5x1.5mm_Drill0.7mm
TP701: +3V3; TestPoint_Keystone_5000-5004_Miniature
TP702: PICO_RUN; TestPoint_THTPad_1.5x1.5mm_Drill0.7mm
TP801: J12_GPIO09; TestPoint_THTPad_1.5x1.5mm_Drill0.7mm
TP802: J12_GPIO12; TestPoint_THTPad_1.5x1.5mm_Drill0.7mm
TP1001: FAN_TACH; TestPoint_THTPad_1.5x1.5mm_Drill0.7mm
U201, U202, U801, U802: PC817; DIP-4_W7.62mm
U301: MIC5014; DIP-8_W7.62mm_Socket
U302: 74HCT08; DIP-14_W7.62mm_Socket
U401: R-78E5.0-1.0; Converter_DCDC_RECOM_R-78E-0.5_THT
U402: TL431; TO-92_Inline
U601: MCP2221A; DIP-14_W7.62mm_Socket
U602: MCP1700-3302E/TO; TO-92_Inline

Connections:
+3V3: C701.1, D1002.1, MOD701.36, R202.1, R203.1, R314.1, R405.1, R415.1, R507.1, R1001.1, TP701.1
+5V: C303.1, C403.1, D402.2, J1003.2, R409.1, TP402.1, U302.10, U302.14, U401.3
AND_MAIN: R305.1, U302.3
AND_PRE: R311.1, U302.6
BAT: C101.1, C102.1, C103.1, C104.1, C301.1, C302.1, D101.1, F501.2, J101.1, MOD401.1, Q301.2, Q302.2, Q303.2, Q304.3, R309.1, R401.1, TP101.1, U301.1
BAT_SENSE: C704.1, MOD701.32, R703.2, R704.1
BMS_GND: C201.2, J201.4, U202.3
BMS_OPT1_A: R201.2, U201.1
BMS_OPT2_A: R203.2, U202.1
BMS_RX: MOD701.2, R202.2, U201.4
BMS_RXD: J201.3, R204.2, U202.4
BMS_TX: MOD701.1, U202.2
BMS_TXD: J201.2, U201.2
BMS_VDD: C201.1, J201.1, R201.1, R204.1
BTN_B: Q401.2, R403.2, R404.1
BTN_HI: J1002.1, R401.2, SW401.1
BUTTON_N: MOD701.17, Q401.3, R405.2
CAM_VIN: D406.1, F403.2, MOD402.1
CHG_B1: Q502.2, R503.2, R504.1
CHG_B2: Q503.2, R505.2, R506.1
CHG_C: Q502.3, R502.2
CHG_G: C502.2, Q501.1, R501.2, R502.1
CHG_GND: C501.2, D501.2, MOD501.2, MOD502.2, Q502.1, Q503.1, R504.2, R506.2, TP502.1
CHG_IN: C501.1, D501.1, D502.1, MOD501.1, MOD502.1, TP501.1
CHG_OUT: MOD502.3, Q501.2
CHG_PRESENT_N: MOD701.20, Q503.3, R507.2
CHG_RB: C502.1, F501.1, Q501.3, R501.1
CHG_STAT_N_TO_JETSON: MOD701.26, R813.1
CHG_Z: D502.2, R503.1, R505.1
COMM_ADC2: J903.6, R901.2
COMM_GND: J903.2, R905.1
COMM_RX: J903.4, R803.2
COMM_TX: J903.3, R804.1
CON_3V3: C601.1, C602.1, C604.1, R601.1, U601.1, U601.11, U602.3
CON_RST: R601.2, U601.4
CON_RX: R603.2, U601.5
CON_TX: R602.1, U601.6
DEVKIT_PWR: MOD701.29, R413.1, R415.2
DEV_B: Q403.2, R413.2, R414.1
ESTOP_IN: D1001.1, D1002.2, J1001.2, R1002.1
ESTOP_OK: C1001.1, MOD701.14, R1002.2, R1003.1, U302.2, U302.5
ESTOP_OK_TO_JETSON: MOD701.25, R812.1
ESTOP_SRC: J1001.1, R1001.2
FAN_G: Q1001.2, R1004.2, R1005.1
FAN_PWM: MOD701.21, R1004.1
FAN_PWM_N: J1003.4, Q1001.3
FAN_TACH: J1003.3, TP1001.1
FET_NTC: C304.1, MOD701.34, R316.2
GND: C101.2, C102.2, C103.2, C104.2, C301.2, C302.2, C303.2, C304.2, C401.2, C402.2, C403.2, C404.2, C405.2, C601.2, C602.2, C603.2, C604.2, C701.2, C702.2, C703.2, C704.2, C1001.2, D101.2, D301.2, D302.1, D401.2, D403.1, D404.2, D405.2, D406.2, D701.1, D702.1, D1001.2, J102.1, J402.1, J403.3, J405.1, J406.3, J408.1, J409.2, J601.4, J601.5, J603.4, J801.6, J801.9, J801.14, J801.20, J801.25, J801.30, J801.34, J802.7, J802.9, J802.11, J902.1, J1003.1, MOD401.3, MOD402.2, MOD502.4, MOD601.4, MOD601.8, MOD601.12, MOD601.16, MOD601.20, MOD701.3, MOD701.8, MOD701.13, MOD701.18, MOD701.23, MOD701.28, MOD701.33, MOD701.38, Q305.1, Q401.1, Q403.1, Q406.1, Q1001.1, R306.2, R307.2, R308.2, R312.2, R402.2, R404.2, R407.2, R414.2, R417.2, R424.2, R604.2, R702.2, R704.2, R805.2, R807.2, R808.2, R810.2, R902.2, R904.2, R905.2, R906.2, R1003.2, R1005.2, SW801.2, TH301.2, TP102.1, TP1002.1, U201.3, U301.4, U302.7, U302.12, U302.13, U401.2, U402.2, U601.14, U602.1, U801.2, U801.3, U802.2, U802.3
HUB_VBUS: C603.1, J601.1, J602.1, J603.1, MOD601.1, MOD601.5, MOD601.9, MOD601.13, MOD601.17, U602.2
I2C0_SCL: MOD701.7, R802.2
I2C0_SDA: MOD701.6, R801.2
J12_3V3: J801.17, R806.1
J12_CHG_STAT_N: J801.32, R813.2
J12_CTS: J801.36, R805.1
J12_ESTOP_OK: J801.33, R812.2
J12_GPIO09: J801.7, TP801.1
J12_GPIO12: J801.15, TP802.1
J12_JETSON_UP: J801.31, R808.1, R809.1
J12_LIDAR_REQ: J801.29, R810.1, R811.1
J12_RXD: J801.10, R804.2
J12_SCL: J801.5, R802.1
J12_SDA: J801.3, R801.1
J12_TXD: J801.8, R803.1
J14_CON_RXD: J802.3, R602.2
J14_CON_TXD: J802.4, R603.1
J14_PWR_KEY_N: J802.12, U801.4
J14_RECOVERY_N: J802.10, SW801.1
J14_RESET_N: J802.8, U802.4
JETSON_3V3_SENSE: MOD701.16, R806.2, R807.1
JETSON_PWR_KEY: MOD701.10, R814.1
JETSON_RESET: MOD701.11, R815.1
JETSON_UP: MOD701.15, R809.2
LATCH_OFF: MOD701.12, R406.1
LATCH_OFF_M: MOD401.5, R406.2, R407.1
LATCH_ON: C401.1, J1002.2, MOD401.4, R402.1, R403.1, SW401.2
LED5_A: D403.2, R409.2
LEDF_A: D702.2, R706.2
LEDS_A: D701.2, R705.2
LED_FAULT: MOD701.24, R706.1
LED_STATUS: MOD701.22, R705.1
LIDAR_EN: MOD701.9, R423.1
LIDAR_REQ: MOD701.27, R811.2
LIDAR_V: D405.1, F402.2, J409.1
LID_B: Q406.2, R423.2, R424.1
LID_C: Q406.3, R422.2
LID_G: C406.2, Q405.1, R421.2, R422.1
LID_SW: F402.1, Q405.2
MAIN_EN: MOD701.5, R307.1, U302.1
MIC_IN: R305.2, R306.1, U301.2
NTC_NODE: R314.2, R316.1, TH301.1
OV_B: Q404.2, R419.2, R420.1
OV_C: Q403.3, R412.2
OV_G: C407.2, Q402.1, Q404.3, R411.2, R412.1, R418.1
OV_K: R420.2, U402.3
OV_REF: R416.2, R417.1, R418.2, U402.1
P1_DM: J601.2, MOD601.7
P1_DP: J601.3, MOD601.6
P2_DM: MOD601.11, U601.12
P2_DP: MOD601.10, U601.13
P3_DM: J602.2, MOD601.15
P3_DP: J602.3, MOD601.14
P4_DM: J603.2, MOD601.19
P4_DP: J603.3, MOD601.18
PICO_RUN: MOD701.30, TP702.1
PICO_VSYS: C702.1, D402.1, MOD701.39
PRECHARGE_EN: MOD701.4, R308.1, U302.4
PRE_B: Q305.2, R311.2, R312.1
PRE_C: Q305.3, R310.2
PRE_D: F301.1, Q304.2
PRE_F: F301.2, R313.1
PRE_G: Q304.1, R309.2, R310.1
PWRKEY_A: R814.2, U801.1
RESET_A: R815.2, U802.1
SERVO_BUF: R410.1, U302.8
SERVO_IN: R903.2, R904.1, U302.9
SERVO_IN_J: J904.1, R903.1
SERVO_SIG: J406.1, R410.2
SERVO_V: C404.1, J403.2, J404.1, J406.2, TP403.1
SRVIN_GND: J904.3, R906.1
SW_G1: Q301.1, R301.2
SW_G2: Q302.1, R302.2
SW_G3: Q303.1, R303.2
SW_GATE: R301.1, R302.1, R303.1, R304.1, TP302.1, U301.5
V5_IN: C402.1, D401.1, R408.2, U401.1
VDEV: C405.1, J407.1, Q402.2
VDEV_F: C407.1, D404.1, F401.2, Q402.3, Q404.1, R411.1, R416.1, R419.1
VESC_KILL: MOD701.19, R901.1, R902.1
VM: D301.1, J401.1, J901.1, Q301.3, Q302.3, Q303.3, R304.2, R313.2, R315.1, R701.1, TP301.1, U301.3
VM_LED_A: D302.2, R315.2
VM_SENSE: C703.1, MOD701.31, R701.2, R702.1
VSYS_SW: C406.1, F401.1, F403.1, J410.1, MOD401.2, Q405.3, R408.1, R421.1, R703.1, TP401.1
VUSB_GND: J602.4, R604.1

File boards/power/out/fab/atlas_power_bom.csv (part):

Designator,Qty,Value,Footprint,MPN,Manufacturer,Side,DNP
C101 C102 C103,3,680u 35V,CP_Radial_D12.5mm_P5.00mm,EEU-FM1V681,Panasonic,top (through-hole),
C104 C603 C604,3,1u 50V,C_1206_3216Metric_Pad1.33x1.80mm_HandSolder,KEMET C1206C105K5RACTU (1 uF 50 V X7R 1206),KEMET,bottom (SMD),
D101,1,1.5KE20A,D_DO-201AD_P5.08mm_Vertical_KathodeUp,1.5KE20A,Yageo / Littelfuse,top (through-hole),
TP101 TP102 TP301 TP401 TP402 TP403 TP701 TP1002,8,BAT,TestPoint_Keystone_5000-5004_Miniature,Keystone 5000 (red) / 5001 (black),Keystone,top (through-hole),
J201,1,BMS_UART,JST_XH_B4B-XH-A_1x04_P2.50mm_Vertical,B4B-XH-A(LF)(SN),JST,top (through-hole),
U201 U202 U801 U802,4,PC817,DIP-4_W7.62mm,PC817X2NSZ9F,Sharp,top (through-hole),
R201 R305 R406 R602 R804 R812 R813 R901 R1001,9,1k,R_1206_3216Metric_Pad1.30x1.75mm_HandSolder,RC1206FR-071KL,Yageo,bottom (SMD),R805
R202 R204 R311 R315 R413 R420 R423,7,4.7k,R_1206_3216Metric_Pad1.30x1.75mm_HandSolder,RC1206FR-074K7L,Yageo,bottom (SMD),
R203 R419 R705 R706 R814 R815,6,470,R_1206_3216Metric_Pad1.30x1.75mm_HandSolder,RC1206FR-07470RL,Yageo,bottom (SMD),
C201 C302 C303 C304 C401 C406 C407 C502 C601 C602 C701 C703 C704,13,100n,C_1206_3216Metric_Pad1.33x1.80mm_HandSolder,Samsung CL31B104KBCNNNC (100 nF 50 V X7R 1206),Samsung,bottom (SMD),
Q301 Q302 Q303,3,IRFB7430PBF,TO-220-3_Vertical,IRFB7430PBF,Infineon,top (through-hole),
R301 R302 R303,3,10,R_1206_3216Metric_Pad1.30x1.75mm_HandSolder,RC1206FR-0710RL,Yageo,bottom (SMD),
R304,1,2.2M,R_1206_3216Metric_Pad1.30x1.75mm_HandSolder,RC1206FR-072M2L,Yageo,bottom (SMD),
U301,1,MIC5014,DIP-8_W7.62mm_Socket,MIC5014YN,Microchip,top (through-hole),
C301 C402 C403 C501 C702,5,10u 50V,C_1210_3225Metric_Pad1.33x2.70mm_HandSolder,Samsung CL32B106KBJNNNE (10 uF 50 V X7R 1210),Samsung,bottom (SMD),
R306 R307 R308 R312 R404 R407 R414 R416 R424 R701 R703 R807 R808 R810 R902 R904 R1005,17,100k,R_1206_3216Metric_Pad1.30x1.75mm_HandSolder,RC1206FR-07100KL,Yageo,bottom (SMD),
U302,1,74HCT08,DIP-14_W7.62mm_Socket,SN74HCT08N,Texas Instruments,top (through-hole),
Q304 Q405,2,IRF9Z34NPBF,TO-220-3_Vertical,IRF9Z34NPBF,Infineon,top (through-hole),
R309 R310 R314 R316 R402 R405 R411 R415 R421 R422 R501 R507 R601 R603 R803 R806 R809 R811 R903 R1003,20,10k,R_1206_3216Metric_Pad1.30x1.75mm_HandSolder,RC1206FR-0710KL,Yageo,bottom (SMD),
Q305 Q401 Q403 Q406 Q502 Q503,6,2N3904,TO-92_Inline,2N3904BU,onsemi,top (through-hole),
F301,1,MF-R050,Fuse_Bourns_MF-R_P5.08mm,MF-R050,Bourns,top (through-hole),
R313,1,10 5W,R_Axial_Power_L25.0mm_W9.0mm_P27.94mm,SQP500JB-10R,Yageo,top (through-hole),
D301,1,1.5KE22A,D_DO-201AD_P5.08mm_Vertical_KathodeUp,1.5KE22A,Diotec,top (through-hole),
TH301,1,10k B3977,C_Disc_D3.0mm_W2.0mm_P2.50mm,NTCLE100E3103JB0,Vishay,top (through-hole),
HS301,1,HEATSINK_BAR,Heatsink_Bar_3xTO220_40x15x3mm,"6061 bar 40 x 15 x 3 mm, 3 x 3.2 mm holes at 13.0 mm",SendCutSend or stock bar,mechanical,
D302 D702,2,RED,LED_D3.0mm,Lite-On LTL-4221N (3 mm red),Lite-On,top (through-hole),
MOD401,1,POLOLU_2813,WireLand_Pololu_2813,2813,Pololu,"module off board, wired",
SW401,1,POWER,SW_Tactile_SPST_Angled_PTS645Vx58-2LFS,PTS645VL58-2 LFS,C&K,top (through-hole),
R401,1,33k,R_1206_3216Metric_Pad1.30x1.75mm_HandSolder,RC1206FR-0733KL,Yageo,bottom (SMD),
R403,1,22k,R_1206_3216Metric_Pad1.30x1.75mm_HandSolder,RC1206FR-0722KL,Yageo,bottom (SMD),
R408,1,4.7,R_Axial_DIN0207_L6.3mm_D2.5mm_P7.62mm_Horizontal,Vishay MBB02070C4708FCT00 (0.6 W metal film),Vishay,top (through-hole),
D401,1,P6KE20A,D_DO-15_P3.81mm_Vertical_KathodeUp,P6KE20A,Littelfuse,top (through-hole),
U401,1,R-78E5.0-1.0,Converter_DCDC_RECOM_R-78E-0.5_THT,R-78E5.0-1.0,RECOM,top (through-hole),
D402,1,1N5817,D_DO-41_SOD81_P3.81mm_Vertical_KathodeUp,1N5817RLG,onsemi,top (through-hole),
R409,1,2.2k,R_1206_3216Metric_Pad1.30x1.75mm_HandSolder,RC1206FR-072K2L,Yageo,bottom (SMD),
D403 D701,2,GREEN,LED_D3.0mm,Lite-On LTL-4231N (3 mm green),Lite-On,top (through-hole),
J403 J406 J904,3,BEC_OUT,PinHeader_1x03_P2.54mm_Vertical,Wurth 61300311121,Wurth,top (through-hole),
C404,1,1000u 16V,CP_Radial_D10.0mm_P5.00mm,EEU-FM1C102,Panasonic,top (through-hole),
R410,1,220,R_1206_3216Metric_Pad1.30x1.75mm_HandSolder,RC1206FR-07220RL,Yageo,bottom (SMD),
F401 F501,2,5A mini,Fuseholder_Blade_Mini_Keystone_3568,Keystone 3568 + Littelfuse 0297005.WXNV,Keystone / Littelfuse,top (through-hole),
D404 D405 D406,3,P6KE22A,D_DO-15_P3.81mm_Vertical_KathodeUp,P6KE22A,Taiwan Semiconductor,top (through-hole),
Q402 Q501,2,IRF4905PBF,TO-220-3_Vertical,IRF4905PBF,Infineon,top (through-hole),
R412 R502,2,6.8k,R_1206_3216Metric_Pad1.30x1.75mm_HandSolder,RC1206FR-076K8L,Yageo,bottom (SMD),
U402,1,TL431,TO-92_Inline,TL431ACLP,Texas Instruments,top (through-hole),
R417,1,15.0k,R_1206_3216Metric_Pad1.30x1.75mm_HandSolder,RC1206FR-0715KL,Yageo,bottom (SMD),
R418,1,1.2M,R_1206_3216Metric_Pad1.30x1.75mm_HandSolder,RC1206FR-071M2L,Yageo,bottom (SMD),
Q404,1,2N3906,TO-92_Inline,2N3906BU,onsemi,top (through-hole),
C405,1,150u 35V,CP_Radial_D8.0mm_P3.50mm,Panasonic EEU-FM1V151,Panasonic,top (through-hole),
F402 F403,2,MF-R075,Fuse_Bourns_MF-R_P5.08mm,MF-R075,Bourns,top (through-hole),
J409,1,LIDAR_PWR,"TerminalBlock_Phoenix_PT-1,5-2-3.5-H_1x02_P3.50mm_Horizontal",1984617,Phoenix Contact,top (through-hole),
MOD402,1,POLOLU_S18V20F12,WireLand_Pololu_S18V20F12,2577 (S18V20F12),Pololu,"module off board, wired",
MOD501,1,ADA5807_HUSB238,WireLand_PD_Trigger,5807,Adafruit,"module off board, wired",
D501,1,P6KE24A,D_DO-15_P3.81mm_Vertical_KathodeUp,P6KE24A,Littelfuse,top (through-hole),
MOD502,1,CCCV_BUCK_XL4015,WireLand_CCCV_Buck,XL4015 CC/CV 5 A module (generic),generic,"module off board, wired",
D502,1,1N5247B,D_DO-35_SOD27_P2.54mm_Vertical_KathodeUp,1N5247BTR,onsemi,top (through-hole),
R503 R504 R505 R506,4,47k,R_1206_3216Metric_Pad1.30x1.75mm_HandSolder,RC1206FR-0747KL,Yageo,bottom (SMD),
MOD601,1,ADA5997_CH334F_HUB,Adafruit_5997_CH334F_Hub_Headers,5997,Adafruit,module on sockets,
J601,1,DEVKIT_USB,USB_A_Wuerth_614004134726_Horizontal,Wurth 614004134726,Wurth,top (through-hole),
J602 J603,2,VESC_USB,PinHeader_1x04_P2.54mm_Vertical,Wurth 61300411121,Wurth,top (through-hole),
U601,1,MCP2221A,DIP-14_W7.62mm_Socket,MCP2221A-I/P,Microchip,top (through-hole),
U602,1,MCP1700-3302E/TO,TO-92_Inline,MCP1700-3302E/TO,Microchip,top (through-hole),
R604,1,2.2,R_1206_3216Metric_Pad1.30x1.75mm_HandSolder,RC1206FR-072R2L,Yageo,bottom (SMD),
MOD701,1,RPi_Pico,RaspberryPi_Pico_Socketed_2x20_P17.78mm,SC0915,Raspberry Pi,module on sockets,
R702 R704,2,18k,R_1206_3216Metric_Pad1.30x1.75mm_HandSolder,RC1206FR-0718KL,Yageo,bottom (SMD),
J801,1,J12_RIBBON,IDC-Header_2x20_P2.54mm_Vertical,Wurth 61204021621,Wurth,top (through-hole),
-,0,330,R_1206_3216Metric_Pad1.30x1.75mm_HandSolder,RC1206FR-07330RL,Yageo,bottom (SMD),R801 R802
J802,1,J14_HARNESS,PinHeader_1x12_P2.54mm_Vertical,Wurth 61301211121,Wurth,top (through-hole),
SW801,1,RECOVERY,SW_PUSH_6mm_H5mm,PTS645SL50-2 LFS,C&K,top (through-hole),
J903,1,FSESC_COMM,JST_PH_B7B-PH-K_1x07_P2.00mm_Vertical,B7B-PH-K-S(LF)(SN),JST,top (through-hole),
R905 R906,2,3.3,R_1206_3216Metric_Pad1.30x1.75mm_HandSolder,RC1206FR-073R3L,Yageo,bottom (SMD),
J1001,1,ESTOP,JST_PH_B2B-PH-K_1x02_P2.00mm_Vertical,B2B-PH-K-S(LF)(SN),JST,top (through-hole),
R1002 R1004,2,100,R_1206_3216Metric_Pad1.30x1.75mm_HandSolder,RC1206FR-07100RL,Yageo,bottom (SMD),
C1001,1,10n,C_1206_3216Metric_Pad1.33x1.80mm_HandSolder,KEMET C1206C103K5RACTU (10 nF 50 V X7R 1206),KEMET,bottom (SMD),
D1001 D1002,2,BAT85,D_DO-35_SOD27_P2.54mm_Vertical_KathodeUp,BAT85S-TAP,Vishay,top (through-hole),
J1002,1,BTN_REMOTE,JST_PH_S2B-PH-K_1x02_P2.00mm_Horizontal,S2B-PH-K-S(LF)(SN),JST,top (through-hole),
J1003,1,FAN,FanPinHeader_1x04_P2.54mm_Vertical,Molex 47053-1000,Molex,top (through-hole),
Q1001,1,2N7000,TO-92_Inline,2N7000-G,Microchip,top (through-hole),
-,1,DIP-8 socket for U301 MIC5014 (soldered in its footprint),-,TE 1-2199298-2,TE Connectivity,through-hole (socket),
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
